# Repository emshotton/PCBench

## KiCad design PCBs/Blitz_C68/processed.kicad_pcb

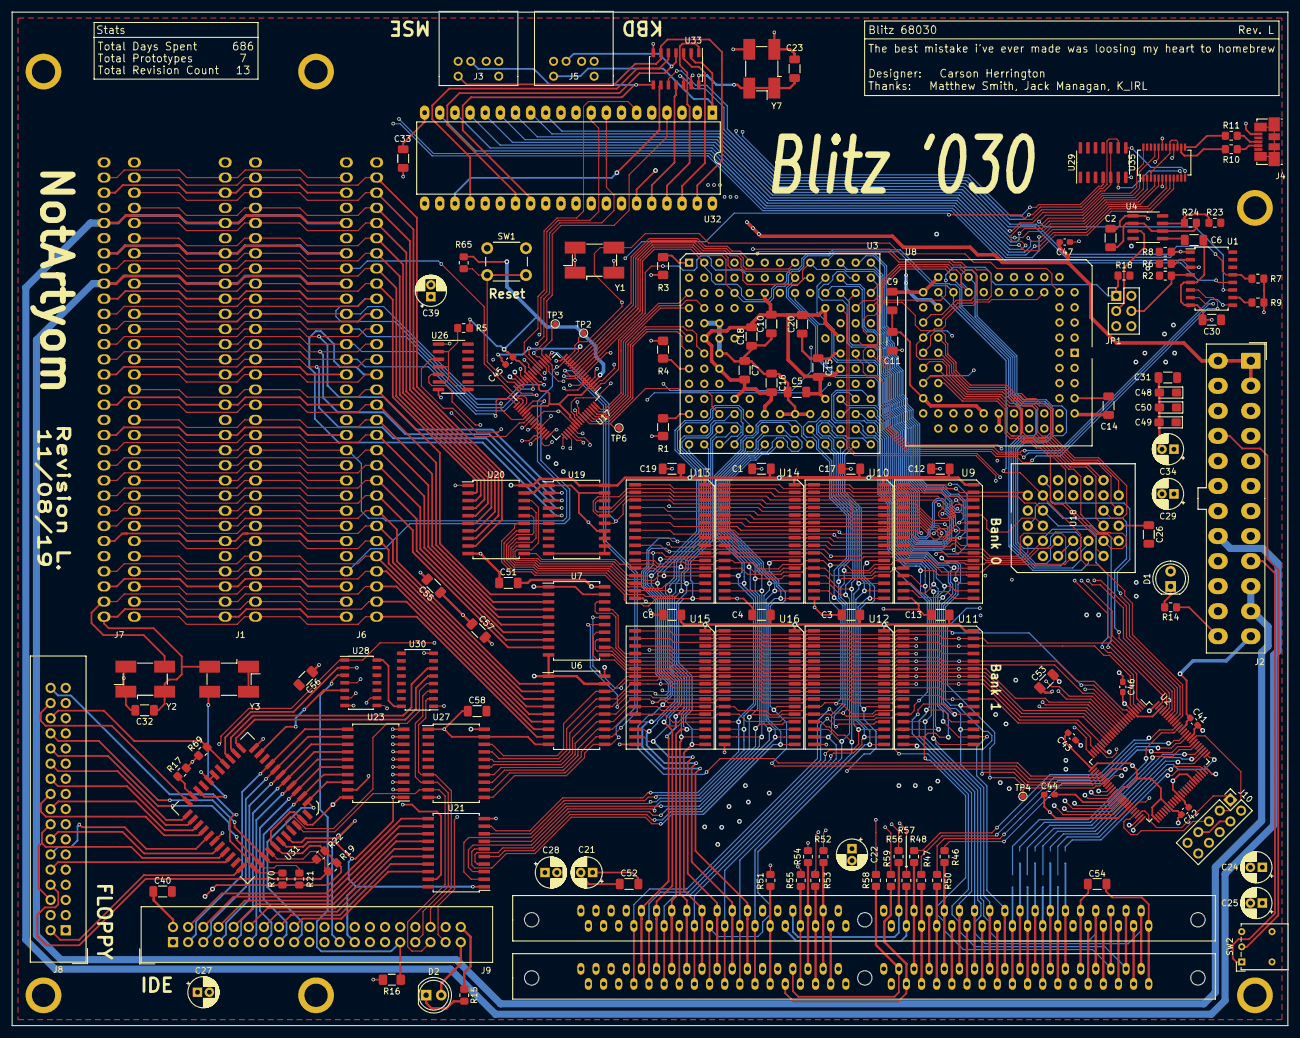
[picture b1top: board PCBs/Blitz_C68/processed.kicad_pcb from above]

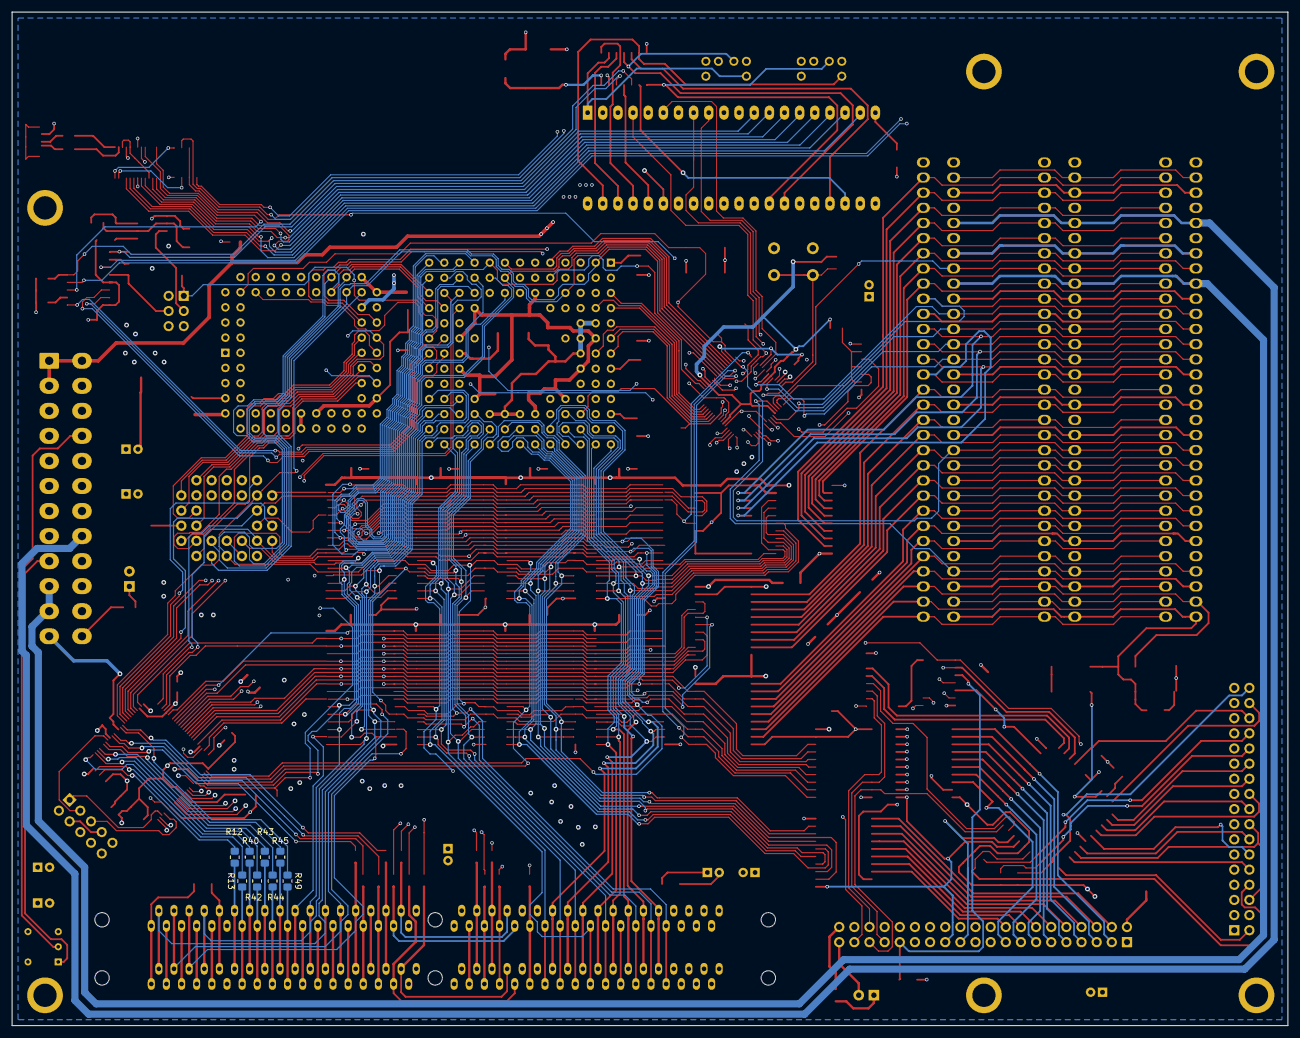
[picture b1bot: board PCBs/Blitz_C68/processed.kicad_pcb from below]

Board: 4 copper layers, 214.0 x 170.0 mm, 160 parts (8 on the bottom side), 278 nets.

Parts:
C1, C3, C4, C5, C7, C8, C9, C10, C11, C12, C13, C14, C15, C16, C17, C18, C19, C20, C23, C26, C30, C31, C32, C33, C40, C51, C52, C53, C54, C55, C56, C57, C58: 100nf; C_1206_3216Metric_Pad1.33x1.80mm_HandSolder
C2: .47uF; C_1206_3216Metric_Pad1.33x1.80mm_HandSolder
C6: 100pF; C_1206_3216Metric_Pad1.33x1.80mm_HandSolder
C21, C22, C24, C25, C27, C28, C29, C34: 47uf; CP_Radial_D5.0mm_P2.00mm
C39: 10uf; CP_Radial_D5.0mm_P2.00mm
C41, C42, C43, C44, C45, C46, C47: 100nf; C_0603_1608Metric_Pad1.08x0.95mm_HandSolder
C48, C49, C50: 1uf; CP_EIA-3216-10_Kemet-I_Pad1.58x1.35mm_HandSolder
D1, D2: LED; LED_D5.0mm
H1, H2, H3, H4, H5, H6: PTH_mount; atx_mounting_hole
J1, J6, J7: ISAx8; ISA_x8_VERT
J2: ATX24; Molex_Mini-Fit_Jr_5566-24A_2x12_P4.20mm_Vertical
J3: MSE; PS2
J4: USB; USB_Micro-B_Molex_47346-0001
J5: KBD; PS2
J8: FLOPPY; IDC-Header_2x17_P2.54mm_Vertical
J9: IDE; IDC-Header_2x20_P2.54mm_Vertical
J10: JTAG; PinHeader_2x05_P2.54mm_Vertical
JP1: Conn_02x03_Odd_Even; PinHeader_2x03_P2.54mm_Vertical
R1, R3, R4, R16: 10k; R_1206_3216Metric_Pad1.42x1.75mm_HandSolder
R2, R5, R6, R7, R8, R9, R14, R18, R23, R24, R65: 10k; R_0805_2012Metric_Pad1.20x1.40mm_HandSolder
R10, R11: 27; R_0805_2012Metric_Pad1.20x1.40mm_HandSolder
R12, R13, R40, R42, R43, R44, R45, R46, R47, R48, R49, R50, R51, R52, R53, R54, R55, R56, R57, R58, R59: 22; R_0805_2012Metric_Pad1.20x1.40mm_HandSolder
R15: 330; R_0805_2012Metric_Pad1.20x1.40mm_HandSolder
R17, R19, R21, R22, R69, R70: 150; R_0805_2012Metric_Pad1.20x1.40mm_HandSolder
SW1: RESET; SW_PUSH_6mm
SW2: PWR; SW_Lever_1P2T_NKK_GW12LxH
TP2, TP3, TP4, TP6: TestPoint; TestPoint_Pad_D1.0mm
U1: 74LS148; SOIC-16W_5.3x10.2mm_P1.27mm
U2: XC9572XL-TQ100; TQFP-100_14x14mm_P0.5mm
U3: M68030; PGA120
U4: TLC555; SOIC-8_3.9x4.9mm_P1.27mm
U5, U24: SIMM_72
U6, U7, U19, U20, U21, U23, U27: 74LS245; SOIC-20W_7.5x12.8mm_P1.27mm
U8: M68882_PLCC; PLCC-68_THT-Socket
U9, U10, U11, U12, U13, U14, U15, U16: AS6C4008; SOIC-32
U17: XC9572XL-VQ64; TQFP-64_10x10mm_P0.5mm
U18: SST39SF040; PLCC-32_TH
U26: 7407; SOIC-14_3.9x8.7mm_P1.27mm
U28: 7404; SOIC-14_3.9x8.7mm_P1.27mm
U29: 7432; SOIC-14_3.9x8.7mm_P1.27mm
U30: 74hc139; SOIC-16_3.9x9.9mm_P1.27mm
U31: WD37C65; PLCC-44
U32: 8042; DIP-40_W15.24mm_LongPads
U33: 74LS06; SOIC-14_3.9x8.7mm_P1.27mm
U35: FT240XS; SSOP-24_3.9x8.7mm_P0.635mm
Y1: 20MHz; Oscillator_SMD_EuroQuartz_XO91-4Pin_7.0x5.0mm_HandSoldering
Y2: 14.316MHz; Oscillator_SMD_EuroQuartz_XO91-4Pin_7.0x5.0mm_HandSoldering
Y3: 16MHz; Oscillator_SMD_EuroQuartz_XO91-4Pin_7.0x5.0mm_HandSoldering
Y7: 8MHz; Oscillator_SMD_EuroQuartz_XO91-4Pin_7.0x5.0mm_HandSoldering

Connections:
100Hz: JP1.3, U4.3 (OUT)
!READ: J9.25, U18.24 (OE), U21.1 (~DIR), U23.1 (~DIR), U28.8, U29.4, U31.1 (/RD), U32.8 (RD)
+3V3: C41.2, C42.2, C43.2, C44.2, C45.2, C46.2, C47.2, J2.1 (3V3), J2.2 (3V3), J2.12 (3V3), J2.13 (3V3), J10.4 (VREF), J10.7 (VCC), R5.1, R65.1, U2.5 (VCC), U2.26 (VCCIO), U2.38 (VCCIO), U2.51 (VCCIO), U2.57 (VCC), U2.88 (VCCIO), U2.98 (VCC), U17.3 (VCC), U17.26 (VCCIO), U17.37 (VCC), U17.55 (VCCIO)
+5V: C1.2, C3.2, C4.2, C5.2, C7.2, C8.2, C9.2, C10.2, C11.2, C12.2, C13.2, C14.2, C15.2, C16.2, C17.2, C18.2, C19.2, C20.2, C21.1, C22.1, C23.2, C24.1, C25.1, C26.2, C27.1, C28.1, C29.1, C30.2, C31.2, C32.2, C33.2, C34.1, C39.1, C40.2, C48.1, C49.1, C50.1, C51.2, C52.2, C53.2, C54.2, C55.2, C56.2, C57.2, C58.2, D1.2 (A), J1.B3 (+5V), J1.B15 (DACK3), J1.B17 (DACK1), J1.B19 (REFRESH), J1.B26 (DACK2), J1.B29 (+5V), J2.4 (5V), J2.6 (5V), J2.21 (5V), J2.22 (5V), J2.23 (5V), J3.4 (VCC), J5.4 (VCC), J6.B3 (+5V), J6.B15 (DACK3), J6.B17 (DACK1), J6.B19 (REFRESH), J6.B26 (DACK2), J6.B29 (+5V), J7.B3 (+5V), J7.B15 (DACK3), J7.B17 (DACK1), J7.B19 (REFRESH), J7.B26 (DACK2), J7.B29 (+5V), J9.29, R1.1, R2.1, R3.1, R4.1, R6.1, R7.1, R8.1, R9.1, R17.2, R18.1, R19.2, R21.2, R22.2, R23.2, R69.2, R70.2, U1.16 (VCC), U3.C6 (VCC), U3.D4 (VCC), U3.D10 (VCC), U3.F2 (VCC), U3.F11 (VCC), U3.H3 (VCC), U3.H11 (VCC), U3.K4 (VCC), U3.K10 (VCC), U3.L6 (VCC), U4.4 (~RESET), U4.8 (VDD), U5.10 (VCC), U5.30 (VCC), U5.59 (VCC), U6.20 (VCC), U7.20 (VCC), U8.10 (VCC), U8.16 (VCC), U8.17 (VCC), U8.18 (SIZE), U8.26 (A0), U8.27 (VCC), U8.43 (VCC), U8.52 (VCC), U8.53 (VCC), U8.61 (VCC), U9.32 (VCC), U10.32 (VCC), U11.32 (VCC), U12.32 (VCC), U13.32 (VCC), U14.32 (VCC), U15.32 (VCC), U16.32 (VCC), U18.32 (VCC), U19.20 (VCC), U20.20 (VCC), U21.20 (VCC), U23.20 (VCC), U24.10 (VCC), U24.30 (VCC), U24.59 (VCC), U26.14 (VCC), U27.20 (VCC), U28.14 (VCC), U29.14 (VCC), U30.16 (VCC), U31.5 (/DACK), U31.44 (VCC), U32.5 (SS), U32.25 (PROG), U32.26 (VDD), U32.40 (VCC), U33.14 (VCC), U35.18 (VCC), Y1.1 (E), Y1.4 (VCC), Y2.1 (E), Y2.4 (VCC), Y3.1 (E), Y3.4 (VCC), Y7.1 (E), Y7.4 (VCC)
+12V: J1.B9 (+12v), J2.10 (12V), J2.11 (12V), J6.B9 (+12v), J7.B9 (+12v)
-5V: J1.B5 (-5V), J2.20 (-5V), J6.B5 (-5V), J7.B5 (-5V)
-12V: J1.B7 (-12V), J2.14 (-12), J6.B7 (-12V), J7.B7 (-12V)
/A0: U3.A2 (A0), U6.11 (B7), U17.8, U18.12 (A0), U27.11 (B7), U32.9 (A0)
/A1: U3.C4 (A1), U6.12 (B6), U8.25 (A1), U17.9, U18.11 (A1), U27.12 (B6)
/A2: U2.93, U3.D13 (A2), U6.13 (B5), U8.24 (A2), U9.12 (A0), U10.12 (A0), U11.12 (A0), U12.12 (A0), U13.12 (A0), U14.12 (A0), U15.12 (A0), U16.12 (A0), U18.10 (A2), U27.13 (B5)
/A3: U2.94, U3.D12 (A3), U6.14 (B4), U8.23 (A3), U9.11 (A1), U10.11 (A1), U11.11 (A1), U12.11 (A1), U13.11 (A1), U14.11 (A1), U15.11 (A1), U16.11 (A1), U18.9 (A3), U27.14 (B4)
/A4: U2.96, U3.C13 (A4), U6.15 (B3), U8.22 (A4), U9.10 (A2), U10.10 (A2), U11.10 (A2), U12.10 (A2), U13.10 (A2), U14.10 (A2), U15.10 (A2), U16.10 (A2), U18.8 (A4), U27.15 (B3)
/A5: U2.97, U3.C12 (A5), U6.16 (B2), U9.9 (A3), U10.9 (A3), U11.9 (A3), U12.9 (A3), U13.9 (A3), U14.9 (A3), U15.9 (A3), U16.9 (A3), U18.7 (A5), U27.16 (B2)
/A6: U2.3 (I/O/GTS1), U3.D11 (A6), U6.17 (B1), U9.8 (A4), U10.8 (A4), U11.8 (A4), U12.8 (A4), U13.8 (A4), U14.8 (A4), U15.8 (A4), U16.8 (A4), U18.6 (A6), U27.17 (B1)
/A7: U2.18, U3.B13 (A7), U6.18 (B0), U9.7 (A5), U10.7 (A5), U11.7 (A5), U12.7 (A5), U13.7 (A5), U14.7 (A5), U15.7 (A5), U16.7 (A5), U18.5 (A7), U27.18 (B0)
/A8: U2.16, U3.B12 (A8), U7.11 (B7), U9.6 (A6), U10.6 (A6), U11.6 (A6), U12.6 (A6), U13.6 (A6), U14.6 (A6), U15.6 (A6), U16.6 (A6), U18.27 (A8)
/A9: U2.10, U3.C11 (A9), U7.12 (B6), U9.5 (A7), U10.5 (A7), U11.5 (A7), U12.5 (A7), U13.5 (A7), U14.5 (A7), U15.5 (A7), U16.5 (A7), U18.26 (A9)
/A10: U2.13, U3.A13 (A10), U7.13 (B5), U9.27 (A8), U10.27 (A8), U11.27 (A8), U12.27 (A8), U13.27 (A8), U14.27 (A8), U15.27 (A8), U16.27 (A8), U18.23 (A10)
/A11: U2.17, U3.C10 (A11), U7.14 (B4), U9.26 (A9), U10.26 (A9), U11.26 (A9), U12.26 (A9), U13.26 (A9), U14.26 (A9), U15.26 (A9), U16.26 (A9), U18.25 (A11)
/A12: U2.23 (I/O/GCK2), U3.B11 (A12), U7.15 (B3), U9.23 (A10), U10.23 (A10), U11.23 (A10), U12.23 (A10), U13.23 (A10), U14.23 (A10), U15.23 (A10), U16.23 (A10), U18.4 (A12)
/A13: U2.20, U3.A12 (A13), U7.16 (B2), U9.25 (A11), U10.25 (A11), U11.25 (A11), U12.25 (A11), U13.25 (A11), U14.25 (A11), U15.25 (A11), U16.25 (A11), U18.28 (A13)
/A14: U2.92, U3.B10 (A14), U7.17 (B1), U9.4 (A12), U10.4 (A12), U11.4 (A12), U12.4 (A12), U13.4 (A12), U14.4 (A12), U15.4 (A12), U16.4 (A12), U18.29 (A14)
/A15: U2.6, U3.A11 (A15), U7.18 (B0), U9.28 (A13), U10.28 (A13), U11.28 (A13), U12.28 (A13), U13.28 (A13), U14.28 (A13), U15.28 (A13), U16.28 (A13), U18.3 (A15)
/A16: U2.95, U3.B9 (A16), U9.3 (A14), U10.3 (A14), U11.3 (A14), U12.3 (A14), U13.3 (A14), U14.3 (A14), U15.3 (A14), U16.3 (A14), U17.17 (I/O/GCK3), U18.2 (A16), U19.15 (B3)
/A17: U2.99 (I/O/GSR), U3.A10 (A17), U9.31 (A15), U10.31 (A15), U11.31 (A15), U12.31 (A15), U13.31 (A15), U14.31 (A15), U15.31 (A15), U16.31 (A15), U18.30 (A17), U19.16 (B2)
/A18: U2.1 (I/O/GTS3), U3.C8 (A18), U9.2 (A16), U10.2 (A16), U11.2 (A16), U12.2 (A16), U13.2 (A16), U14.2 (A16), U15.2 (A16), U16.2 (A16), U18.1 (A18), U19.17 (B1)
/A19: U2.4 (I/O/GTS2), U3.A9 (A19), U9.30 (A17), U10.30 (A17), U11.30 (A17), U12.30 (A17), U13.30 (A17), U14.30 (A17), U15.30 (A17), U16.30 (A17), U17.10, U19.18 (B0)
/A20: U2.8, U3.B8 (A20), U9.1 (A18), U10.1 (A18), U11.1 (A18), U12.1 (A18), U13.1 (A18), U14.1 (A18), U15.1 (A18), U16.1 (A18), U17.11
/A21: U2.9, U3.A8 (A21), U17.12
/A22: U2.11, U3.B7 (A22)
/A23: U2.12, U3.A7 (A23)
/A24: U2.14, U3.A6 (A24)
/A25: U2.15, U3.B6 (A25)
/A26: U3.A5 (A26), U17.13
/A27: U3.B5 (A27), U17.1
/CAS0: R52.1, U5.40 (CAS0), U24.40 (CAS0)
/CAS1: R53.1, U5.41 (CAS1), U24.41 (CAS1)
/CAS2: R54.1, U5.42 (CAS2), U24.42 (CAS2)
/CAS3: R55.1, U5.43 (CAS3), U24.43 (CAS3)
/D0: U3.K13 (D0), U5.2 (DQ0), U8.3 (D0), U9.13 (D0), U11.13 (D0), U24.2 (DQ0)
/D1: U3.K12 (D1), U5.4 (DQ1), U8.2 (D1), U9.14 (D1), U11.14 (D1), U24.4 (DQ1)
/D2: U3.L13 (D2), U5.6 (DQ2), U8.1 (D2), U9.15 (D2), U11.15 (D2), U24.6 (DQ2)
/D3: U3.M13 (D3), U5.8 (DQ3), U8.68 (D3), U9.17 (D3), U11.17 (D3), U24.8 (DQ3)
/D4: U3.L12 (D4), U5.20 (DQ4), U8.67 (D4), U9.18 (D4), U11.18 (D4), U24.20 (DQ4)
/D5: U3.K11 (D5), U5.22 (DQ5), U8.66 (D5), U9.19 (D5), U11.19 (D5), U24.22 (DQ5)
/D6: U3.M12 (D6), U5.24 (DQ6), U8.65 (D6), U9.20 (D6), U11.20 (D6), U24.24 (DQ6)
/D7: U3.L11 (D7), U5.26 (DQ7), U8.64 (D7), U9.21 (D7), U11.21 (D7), U24.26 (DQ7)
/D8: U3.N13 (D8), U5.49 (DQ8), U8.62 (D8), U10.13 (D0), U12.13 (D0), U24.49 (DQ8)
/D9: U3.M11 (D9), U5.51 (DQ9), U8.60 (D9), U10.14 (D1), U12.14 (D1), U24.51 (DQ9)
/D10: U3.L10 (D10), U5.53 (DQ10), U8.59 (D10), U10.15 (D2), U12.15 (D2), U24.53 (DQ10)
/D11: U3.N12 (D11), U5.55 (DQ11), U8.58 (D11), U10.17 (D3), U12.17 (D3), U24.55 (DQ11)
/D12: U3.M10 (D12), U5.57 (DQ12), U8.57 (D12), U10.18 (D4), U12.18 (D4), U24.57 (DQ12)
/D13: U3.N11 (D13), U5.61 (DQ13), U8.56 (D13), U10.19 (D5), U12.19 (D5), U24.61 (DQ13)
/D14: U3.M9 (D14), U5.63 (DQ14), U8.55 (D14), U10.20 (D6), U12.20 (D6), U24.63 (DQ14)
/D15: U3.N10 (D15), U5.65 (DQ15), U8.54 (D15), U10.21 (D7), U12.21 (D7), U24.65 (DQ15)
/D16: U3.N9 (D16), U5.3 (DQ16), U8.50 (D16), U14.13 (D0), U16.13 (D0), U21.9 (A7), U24.3 (DQ16)
/D17: U3.M8 (D17), U5.5 (DQ17), U8.49 (D17), U14.14 (D1), U16.14 (D1), U21.8 (A6), U24.5 (DQ17)
/D18: U3.N8 (D18), U5.7 (DQ18), U8.48 (D18), U14.15 (D2), U16.15 (D2), U21.7 (A5), U24.7 (DQ18)
/D19: U3.N7 (D19), U5.9 (DQ19), U8.47 (D19), U14.17 (D3), U16.17 (D3), U21.6 (A4), U24.9 (DQ19)
/D20: U3.M7 (D20), U5.21 (DQ20), U8.46 (D20), U14.18 (D4), U16.18 (D4), U21.5 (A3), U24.21 (DQ20)
/D21: U3.N6 (D21), U5.23 (DQ21), U8.45 (D21), U14.19 (D5), U16.19 (D5), U21.4 (A2), U24.23 (DQ21)
/D22: U3.M6 (D22), U5.25 (DQ22), U8.44 (D22), U14.20 (D6), U16.20 (D6), U21.3 (A1), U24.25 (DQ22)
/D23: U3.N5 (D23), U5.27 (DQ23), U8.42 (D23), U14.21 (D7), U16.21 (D7), U21.2 (A0), U24.27 (DQ23)
/D24: U3.M5 (D24), U5.50 (DQ24), U8.40 (D24), U13.13 (D0), U15.13 (D0), U18.13 (D0), U20.18 (B0), U23.2 (A0), U24.50 (DQ24), U32.12 (D0), U35.24 (DATA0)
/D25: U3.N4 (D25), U5.52 (DQ25), U8.39 (D25), U13.14 (D1), U15.14 (D1), U18.14 (D1), U20.17 (B1), U23.3 (A1), U24.52 (DQ25), U32.13 (D1), U35.4 (DATA1)
/D26: U3.N3 (D26), U5.54 (DQ26), U8.38 (D26), U13.15 (D2), U15.15 (D2), U18.15 (D2), U20.16 (B2), U23.4 (A2), U24.54 (DQ26), U32.14 (D2), U35.2 (DATA2)
/D27: U3.M4 (D27), U5.56 (DQ27), U8.37 (D27), U13.17 (D3), U15.17 (D3), U18.17 (D3), U20.15 (B3), U23.5 (A3), U24.56 (DQ27), U32.15 (D3), U35.9 (DATA3)
/D28: U3.N2 (D28), U5.58 (DQ28), U8.36 (D28), U13.18 (D4), U15.18 (D4), U18.18 (D4), U20.14 (B4), U23.6 (A4), U24.58 (DQ28), U32.16 (D4), U35.1 (DATA4)
/D29: U3.M3 (D29), U5.60 (DQ29), U8.35 (D29), U13.19 (D5), U15.19 (D5), U18.19 (D5), U20.13 (B5), U23.7 (A5), U24.60 (DQ29), U32.17 (D5), U35.7 (DATA5)
/D30: U3.L4 (D30), U5.62 (DQ30), U8.34 (D30), U13.20 (D6), U15.20 (D6), U18.20 (D6), U20.12 (B6), U23.8 (A6), U24.62 (DQ30), U32.18 (D6), U35.8 (DATA6)
/D31: U3.N1 (D31), U5.64 (DQ31), U8.33 (D31), U13.21 (D7), U15.21 (D7), U18.21 (D7), U20.11 (B7), U23.9 (A7), U24.64 (DQ31), U32.19 (D7), U35.5 (DATA7)
/IA0: J1.A31 (A0), J6.A31 (A0), J7.A31 (A0), U6.9 (A7)
/IA1: J1.A30 (A1), J6.A30 (A1), J7.A30 (A1), U6.8 (A6)
/IA2: J1.A29 (A2), J6.A29 (A2), J7.A29 (A2), U6.7 (A5)
/IA3: J1.A28 (A3), J6.A28 (A3), J7.A28 (A3), U6.6 (A4)
/IA4: J1.A27 (A4), J6.A27 (A4), J7.A27 (A4), U6.5 (A3)
/IA5: J1.A26 (A5), J6.A26 (A5), J7.A26 (A5), U6.4 (A2)
/IA6: J1.A25 (A6), J6.A25 (A6), J7.A25 (A6), U6.3 (A1)
/IA7: J1.A24 (A7), J6.A24 (A7), J7.A24 (A7), U6.2 (A0)
/IA8: J1.A23 (A8), J6.A23 (A8), J7.A23 (A8), U7.9 (A7)
/IA9: J1.A22 (A9), J6.A22 (A9), J7.A22 (A9), U7.8 (A6)
/IA10: J1.A21 (A10), J6.A21 (A10), J7.A21 (A10), U7.7 (A5)
/IA11: J1.A20 (A11), J6.A20 (A11), J7.A20 (A11), U7.6 (A4)
/IA12: J1.A19 (A12), J6.A19 (A12), J7.A19 (A12), U7.5 (A3)
/IA13: J1.A18 (A13), J6.A18 (A13), J7.A18 (A13), U7.4 (A2)
/IA14: J1.A17 (A14), J6.A17 (A14), J7.A17 (A14), U7.3 (A1)
/IA15: J1.A16 (A15), J6.A16 (A15), J7.A16 (A15), U7.2 (A0)
/IA16: J1.A15 (A16), J6.A15 (A16), J7.A15 (A16), U19.5 (A3)
/IA17: J1.A14 (A17), J6.A14 (A17), J7.A14 (A17), U19.4 (A2)
/IA18: J1.A13 (A18), J6.A13 (A18), J7.A13 (A18), U19.3 (A1)
/IA19: J1.A12 (A19), J6.A12 (A19), J7.A12 (A19), U19.2 (A0)
/ID0: J1.A9 (D0), J6.A9 (D0), J7.A9 (D0), U20.2 (A0)
/ID1: J1.A8 (D1), J6.A8 (D1), J7.A8 (D1), U20.3 (A1)
/ID2: J1.A7 (D2), J6.A7 (D2), J7.A7 (D2), U20.4 (A2)
/ID3: J1.A6 (D3), J6.A6 (D3), J7.A6 (D3), U20.5 (A3)
/ID4: J1.A5 (D4), J6.A5 (D4), J7.A5 (D4), U20.6 (A4)
/ID5: J1.A4 (D5), J6.A4 (D5), J7.A4 (D5), U20.7 (A5)
/ID6: J1.A3 (D6), J6.A3 (D6), J7.A3 (D6), U20.8 (A6)
/ID7: J1.A2 (D7), J6.A2 (D7), J7.A2 (D7), U20.9 (A7)
/IOA0: J9.35, U27.9 (A7), U31.4 (A0)
/IOA1: J9.33, U27.8 (A6), U30.3 (A)
/IOA2: J9.36, U27.7 (A5), U30.2 (B)
/IOD16: J9.4, U21.11 (B7)
/IOD17: J9.6, U21.12 (B6)
/IOD18: J9.8, U21.13 (B5)
/IOD19: J9.10, U21.14 (B4)
/IOD20: J9.12, U21.15 (B3)
/IOD21: J9.14, U21.16 (B2)
/IOD22: J9.16, U21.17 (B1)
/IOD23: J9.18, U21.18 (B0)
/IOD24: J9.17, U23.18 (B0), U31.7 (DB0)
/IOD25: J9.15, U23.17 (B1), U31.8 (DB1)
/IOD26: J9.13, U23.16 (B2), U31.9 (DB2)
/IOD27: J9.11, U23.15 (B3), U31.10 (DB3)
/IOD28: J9.9, U23.14 (B4), U31.11 (DB4)
/IOD29: J9.7, U23.13 (B5), U31.12 (DB5)
/IOD30: J9.5, U23.12 (B6), U31.13 (DB6)
/IOD31: J9.3, U23.11 (B7), U31.14 (DB7)
/QA0: R12.1, U5.12 (A0), U24.12 (A0)
/QA1: R13.1, U5.13 (A1), U24.13 (A1)
/QA2: R40.1, U5.14 (A2), U24.14 (A2)
/QA3: R42.1, U5.15 (A3), U24.15 (A3)
/QA4: R43.1, U5.16 (A4), U24.16 (A4)
/QA5: R44.1, U5.17 (A5), U24.17 (A5)
/QA6: R45.1, U5.18 (A6), U24.18 (A6)
/QA7: R46.1, U5.28 (A7), U24.28 (A7)
/QA8: R47.1, U5.31 (A8), U24.31 (A8)
/QA9: R48.1, U5.32 (A9), U24.32 (A9)
/QA10: R49.1, U5.19 (A10), U24.19 (A10)
/QA11: R50.1, U5.29 (A11), U24.29 (A11)
/RAS0: R56.1, U5.34 (RAS2), U5.44 (RAS0)
/RAS1: R57.1, U5.33 (RAS3), U5.45 (RAS1)
/RAS2: R58.1, U24.34 (RAS2), U24.44 (RAS0)
/RAS3: R59.1, U24.33 (RAS3), U24.45 (RAS1)
AS: U3.J2 (AS), U8.21 (AS), U17.2 (I/O/GTS2)
BYTE0: U2.30, U9.22 (~CS), U11.22 (~CS), U17.52
BYTE1: U2.29, U10.22 (~CS), U12.22 (~CS), U17.51
BYTE2: U2.28, U14.22 (~CS), U16.22 (~CS), U17.50
BYTE3: U2.27 (I/O/GCK3), U13.22 (~CS), U15.22 (~CS), U17.49
CDIS: U3.H12 (CDIS), U17.23
CLK: J1.B20 (CLK), J6.B20 (CLK), J7.B20 (CLK), TP2.1, U2.22 (I/O/GCK1), U3.E1 (CLK), U8.11 (CLK), U17.15 (I/O/GCK1), Y1.3 (OUT)
DRAM_CS: TP4.1, U2.32, U17.42
DRW: R51.1, U5.47 (R/W), U24.47 (R/W)
DS: U3.K2 (DS), U8.20 (DS), U17.4
DSACK0: U3.F1 (DSACK0), U8.31 (DSACK0), U17.60
DSACK1: U3.G2 (DSACK1), U8.32 (DSACK1), U17.61
DTACK_BUS: R5.2, U17.34, U26.2, U26.4, U26.6
ECS: TP3.1, U3.M2 (ECS), U17.18
FC0: U3.D2 (FC0), U17.63
FC1: U3.C1 (FC1), U17.64 (I/O/GSR)
FC2: U3.D1 (FC2), U17.62
FLOPPY: U17.20, U30.1 (~EN)
FPU: U8.29 (CS), U17.57
FTDI_CS: U17.56, U29.5, U29.10
GND: C1.1, C2.1, C3.1, C4.1, C5.1, C6.1, C7.1, C8.1, C9.1, C10.1, C11.1, C12.1, C13.1, C14.1, C15.1, C16.1, C17.1, C18.1, C19.1, C20.1, C21.2, C22.2, C23.1, C24.2, C25.2, C26.1, C27.2, C28.2, C29.2, C30.1, C31.1, C32.1, C33.1, C34.2, C39.2, C40.1, C41.1, C42.1, C43.1, C44.1, C45.1, C46.1, C47.1, C48.2, C49.2, C50.2, C51.1, C52.1, C53.1, C54.1, C55.1, C56.1, C57.1, C58.1, H1.1, H2.1, H3.1, H4.1, H5.1, H6.1, J1.A11 (AEN), J1.B1 (GND), J1.B10 (GND), J1.B31 (GND), J2.3 (GND), J2.5 (GND), J2.7 (GND), J2.15 (GND), J2.17 (GND), J2.18 (GND), J2.19 (GND), J2.24 (GND), J3.3 (GND), J4.5 (GND), J5.3 (GND), J6.A11 (AEN), J6.B1 (GND), J6.B10 (GND), J6.B31 (GND), J7.A11 (AEN), J7.B1 (GND), J7.B10 (GND), J7.B31 (GND), J8.1, J8.3, J8.5, J8.7, J8.9, J8.11, J8.13, J8.15, J8.17, J8.19, J8.21, J8.23, J8.25, J8.27, J8.29, J8.31, J8.33, J9.2, J9.19, J9.22, J9.24, J9.26, J9.30, J9.40, J10.2 (GND), J10.10 (GND), JP1.2, JP1.5, JP1.6, R14.1, R15.1, R16.1, SW1.1 (A), SW2.3 (C), U1.5 (EI), U1.8 (GND), U2.21 (GND), U2.31 (GND), U2.44 (GND), U2.62 (GND), U2.69 (GND), U2.75 (GND), U2.84 (GND), U2.100 (GND), U3.C5 (GND), U3.C7 (GND), U3.C9 (GND), U3.E2 (AVEC), U3.E3 (GND), U3.E11 (GND), U3.F3 (GND), U3.G3 (GND), U3.G11 (GND), U3.J3 (GND), U3.J11 (GND), U3.L5 (GND), U3.L7 (GND), U3.L8 (GND), U3.L9 (GND), U4.1 (GND), U5.1 (GND), U5.39 (GND), U5.72 (GND), U6.1 (~DIR), U6.10 (GND), U6.19 (~CE), U7.1 (~DIR), U7.10 (GND), U7.19 (~CE), U8.5 (GND), U8.6 (GND), U8.7 (GND), U8.8 (GND), U8.9 (GND), U8.12 (GND), U8.14 (GND), U8.19 (GND), U8.30 (GND), U8.41 (GND), U8.51 (GND), U8.63 (GND), U9.16 (GND), U10.16 (GND), U11.16 (GND), U12.16 (GND), U13.16 (GND), U14.16 (GND), U15.16 (GND), U16.16 (GND), U17.14 (GND), U17.21 (GND), U17.41 (GND), U17.54 (GND), U18.16 (GND), U19.1 (~DIR), U19.10 (GND), U19.11 (B7), U19.12 (B6), U19.13 (B5), U19.14 (B4), U19.19 (~CE), U20.10 (GND), U20.19 (~CE)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
HALT: U3.H2 (HALT), U17.16 (I/O/GCK2)
IDE0: J9.37, U17.7
IDE1: J9.38, U17.40
IO_CS: U17.39, U21.19 (~CE), U23.19 (~CE)
IPL0: U1.9 (S0), U3.H13 (IPL0)
IPL1: U1.7 (S1), U3.G13 (IPL1)
IPL2: U1.6 (S2), U3.G12 (IPL2)
IRQ_FLOPPY: U1.3 (I6), U28.6
IRQ_FTDI: U1.11 (I1), U35.21 (~RXF)
IRQ_IDE: U1.12 (I2), U28.4
IRQ_KBD: R8.2, U1.1 (I4), U33.12
IRQ_MSE: R7.2, U1.13 (I3), U33.10
IRQ_SYS: JP1.4, R2.2, U1.4 (I7)
ISA_IRQ0: J1.B25 (IRQ3), J6.B25 (IRQ3), J7.B25 (IRQ3)
ISA_IRQ1: J1.B24 (IRQ4), J6.B24 (IRQ4), J7.B24 (IRQ4)
ISA_IRQ2: J1.B23 (IRQ5), J6.B23 (IRQ5), J7.B23 (IRQ5)
ISA_IRQ3: J1.B22 (IRQ6), J6.B22 (IRQ6), J7.B22 (IRQ6)
ISA_IRQ4: J1.B21 (IRQ7), J6.B21 (IRQ7), J7.B21 (IRQ7)
I_DIR: U17.24, U20.1 (~DIR)
KBD_CS: U17.22, U32.6 (CS)
MMUDIS: JP1.1, R18.2, U3.F13 (MMUDIS)
unnamed: C2.2, R24.1, U4.2 (~TRIG), U4.6 (THRES)
unnamed: C6.2, U4.5 (CONT)
unnamed: D1.1 (K), R14.2
unnamed: D2.1 (K), R15.2
unnamed: D2.2 (A), J9.39
unnamed: J1.A10 (IOCHRRDY), J6.A10 (IOCHRRDY), J7.A10 (IOCHRRDY), U17.38
unnamed: J1.B8 (NOWS), J6.B8 (NOWS), J7.B8 (NOWS), U17.35
unnamed: J1.B11 (MEMW), J6.B11 (MEMW), J7.B11 (MEMW), U17.25
unnamed: J1.B12 (MEMR), J6.B12 (MEMR), J7.B12 (MEMR), U17.27
unnamed: J1.B13 (IOW), J6.B13 (IOW), J7.B13 (IOW), U17.32
unnamed: J1.B14 (IOR), J6.B14 (IOR), J7.B14 (IOR), U17.33
unnamed: J1.B28 (ALE), J6.B28 (ALE), J7.B28 (ALE), U17.36
unnamed: J1.B30 (OSC), J6.B30 (OSC), J7.B30 (OSC), Y2.3 (OUT)
unnamed: J2.9 (5VSB), SW2.1 (A)
unnamed: J2.16 (PS_ON), SW2.2 (B)
unnamed: J3.1 (DATA), U32.28 (P11), U33.8
unnamed: J3.5 (CLK), U32.39 (T1), U33.6
unnamed: J4.2 (D-), R10.2
unnamed: J4.3 (D+), R11.2
unnamed: J5.1 (DATA), U32.27 (P10), U33.4
unnamed: J5.5 (CLK), U32.1 (T0), U33.2
unnamed: J8.2, U31.39 (/RWC/RPM)
unnamed: J8.8, R19.1, U31.43 (/IDX)
unnamed: J8.10, U31.37 (/MO2/DS4)
unnamed: J8.12, U31.33 (/DS1)
unnamed: J8.14, U31.35 (/DS2)
unnamed: J8.6, J8.16, U31.36 (/MO1/DS3)
unnamed: J8.18, U31.31 (/DIRC)
unnamed: J8.20, U31.32 (/STEP)
unnamed: J8.22, U31.30 (/WD)
unnamed: J8.24, U31.29 (/WE)
unnamed: J8.26, R21.1, U31.41 (/WP)
unnamed: J8.28, R22.1, U31.42 (/TR00)
unnamed: J8.30, R69.1, U31.21 (/RDD)
unnamed: J8.32, U31.28 (/HS)
unnamed: J8.34, R70.1, U31.40 (/DCHG)
unnamed: J9.27, U26.5
unnamed: J9.31, R16.2, U28.3
unnamed: J10.9 (TDI), U17.28 (TDI)
unnamed: R1.2, U3.L1 (CIIN)
unnamed: R3.2, U3.A1 (BR)
unnamed: R4.2, U3.H1 (BERR)
unnamed: R6.2, U1.2 (I5)
unnamed: R9.2, U1.10 (IO)
unnamed: R10.1, U35.14 (USBDM)
unnamed: R11.1, U35.13 (USBDP)
unnamed: R12.2, U2.72
unnamed: R13.2, U2.74
unnamed: R17.1, U31.27 (PCVAL)
unnamed: R23.1, R24.2, U4.7 (DISCH)
unnamed: R40.2, U2.76
unnamed: R42.2, U2.77
unnamed: R43.2, U2.78
unnamed: R44.2, U2.79
unnamed: R45.2, U2.81
unnamed: R46.2, U2.82
unnamed: R47.2, U2.86
unnamed: R48.2, U2.90
unnamed: R49.2, U2.89
unnamed: R50.2, U2.85
unnamed: R51.2, U2.35
unnamed: R52.2, U2.40
unnamed: R53.2, U2.39
unnamed: R54.2, U2.37
unnamed: R55.2, U2.36
unnamed: R56.2, U2.49
unnamed: R57.2, U2.50
unnamed: R58.2, U2.41
unnamed: R59.2, U2.42
unnamed: R65.2, SW1.2 (B), U17.31
unnamed: U2.25, U26.3
unnamed: U26.1, U35.20 (~TXE)
unnamed: U28.5, U31.16 (IRQ)
unnamed: U29.6, U35.11 (~RD)
unnamed: U29.8, U35.12 (~WR)
unnamed: U30.4 (~Q0), U31.3 (/CS)
unnamed: U30.5 (~Q1), U31.18 (/LDOR)
unnamed: U30.6 (~Q2), U31.19 (/LDCR)
unnamed: U31.26 (XT1), Y3.3 (OUT)
unnamed: U32.3 (X2), Y7.3 (OUT)
unnamed: U32.23 (P22), U33.9
unnamed: U32.24 (P23), U33.5
unnamed: U32.35 (P24/OB), U33.13
unnamed: U32.36 (P25/BF), U33.11
unnamed: U32.37 (P26/DRQ), U33.1
unnamed: U32.38 (P27/DAK), U33.3
unnamed: U35.3 (VCCIO), U35.15 (3V3OUT), U35.17 (VCCIO)
RESET: J9.1, U2.33, U3.F12 (RESET), U8.13 (RESET), U17.19, U28.1, U32.4 (RESET), U35.16 (~RESET)
RESET_N: J1.B2 (RESET), J6.B2 (RESET), J7.B2 (RESET), U28.2, U31.20 (RST)
ROM: U17.44, U18.22 (CE)
RW0: U9.29 (~WE), U10.29 (~WE), U13.29 (~WE), U14.29 (~WE), U17.48
RW1: U11.29 (~WE), U12.29 (~WE), U15.29 (~WE), U16.29 (~WE), U17.46
RW_N: J9.23, TP6.1, U2.91, U3.L3 (R/W), U8.28 (R/W), U17.58, U18.31 (PGM), U28.9, U29.9, U31.2 (/WR), U32.10 (WR)
SIZ0: U3.L2 (SIZ0), U17.5 (I/O/GTS1)
SIZ1: U3.K3 (SIZ1), U17.6
STERM: U3.G1 (STERM), U17.59
TCK: J10.1 (TCK), U2.48 (TCK), U17.30 (TCK)
TDO1: U2.45 (TDI), U17.53 (TDO)
TDO2: J10.3 (TDO), U2.83 (TDO)
TMS: J10.5 (TMS), U2.47 (TMS), U17.29 (TMS)
_RW0: U9.24 (~OE), U10.24 (~OE), U13.24 (~OE), U14.24 (~OE), U17.47
_RW1: U11.24 (~OE), U12.24 (~OE), U15.24 (~OE), U16.24 (~OE), U17.45

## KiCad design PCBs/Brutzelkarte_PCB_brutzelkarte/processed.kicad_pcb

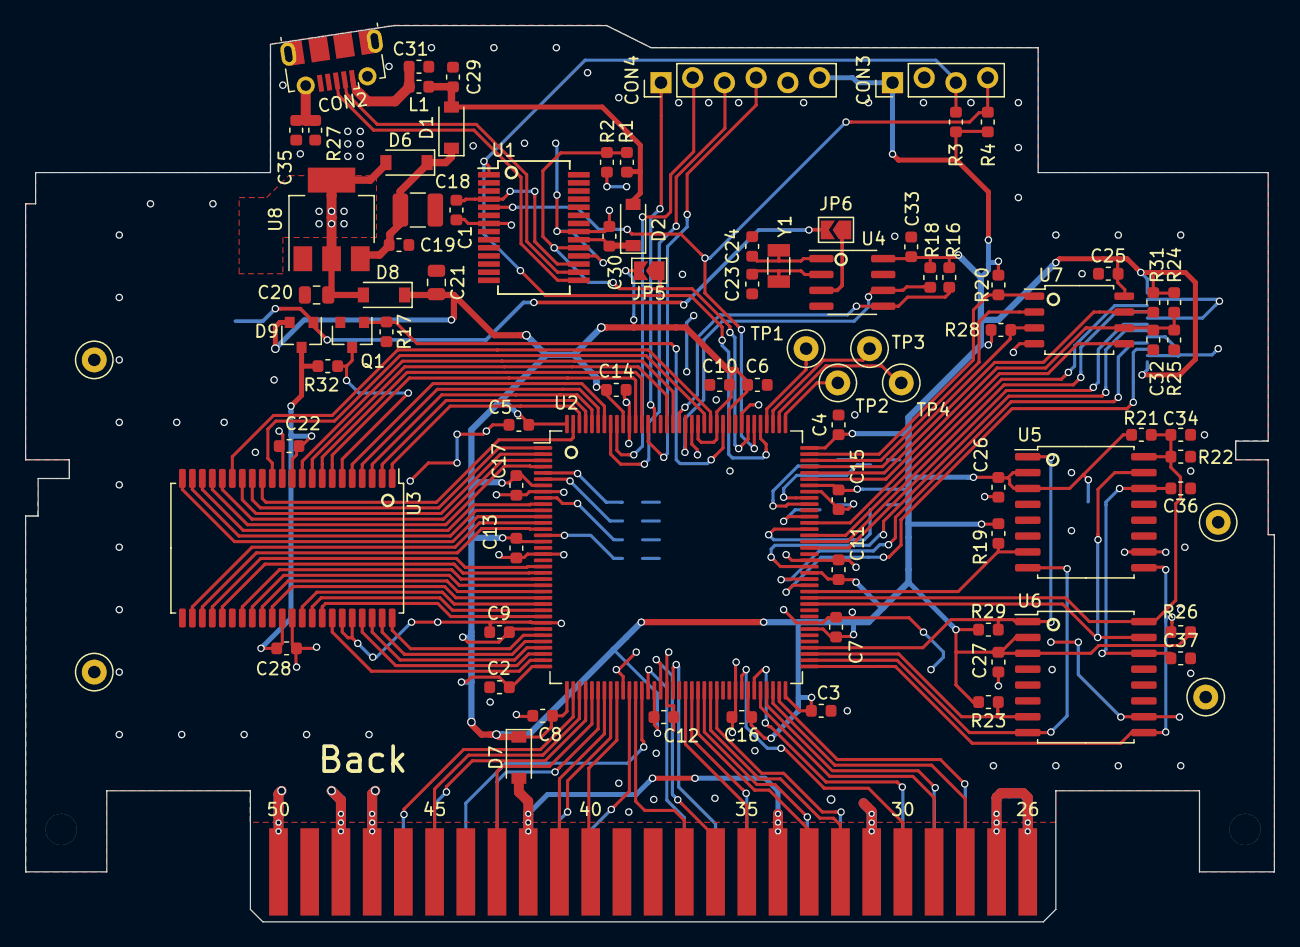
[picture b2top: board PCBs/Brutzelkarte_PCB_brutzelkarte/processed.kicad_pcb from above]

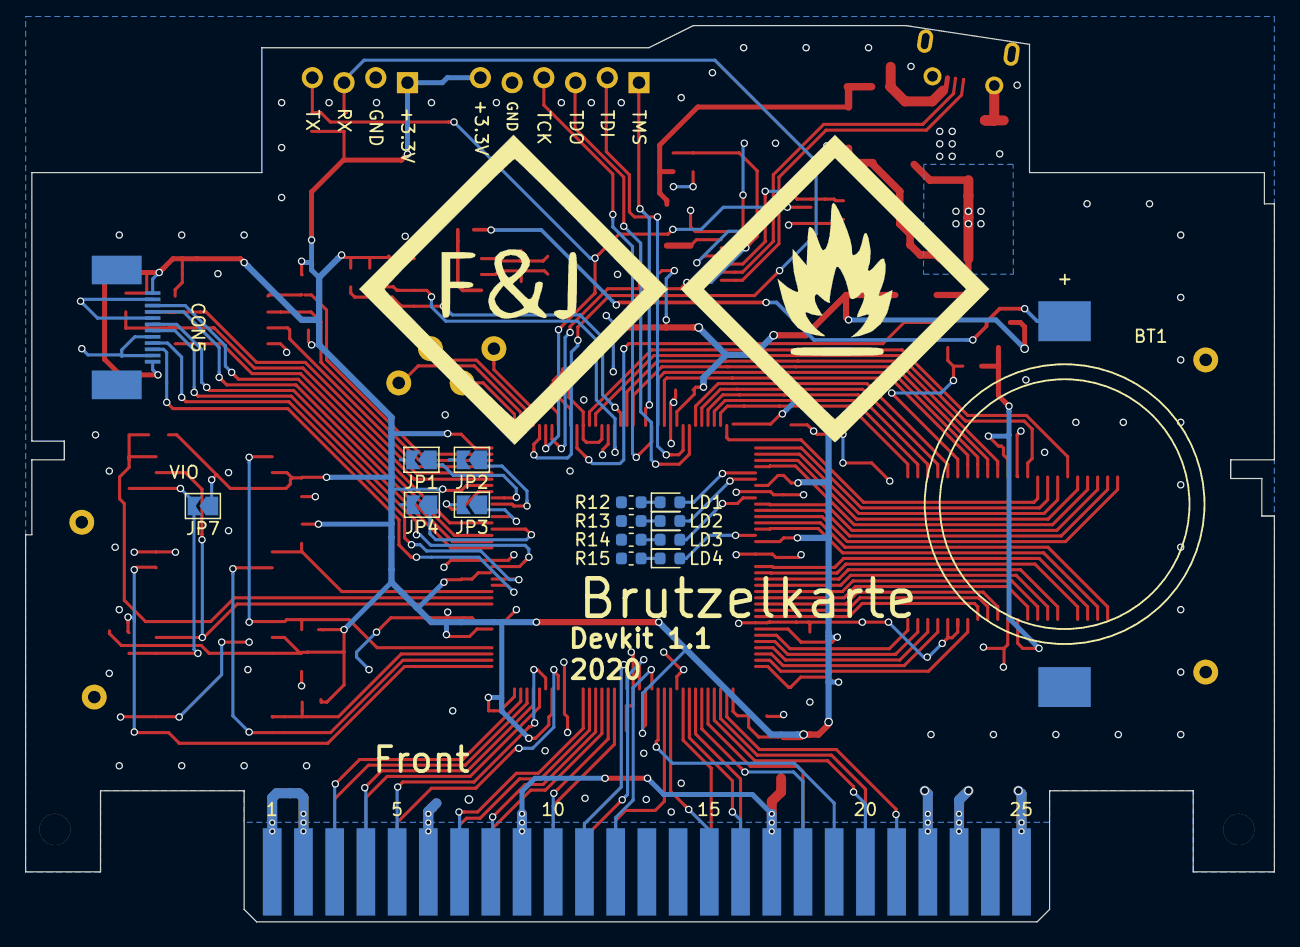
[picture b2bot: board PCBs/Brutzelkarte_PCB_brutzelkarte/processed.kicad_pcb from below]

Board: 2 copper layers, 100.0 x 71.8 mm, 103 parts (16 on the bottom side), 125 nets.

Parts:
BT1: Battery_Cell; BU2032SM
C1, C2, C3, C4, C5, C6, C7, C8, C9, C10, C11, C12, C13, C14, C15, C16, C17, C19, C22, C25, C26, C27, C28, C30, C33, C36, C37: 100n; C_0603_1608Metric
C18: 10u; C_1210_3225Metric
C20: 1u; C_0805_2012Metric
C21: 47u; C_0805_2012Metric
C23, C24: 6-9 pF; C_0603_1608Metric
C29: 4u7; C_0603_1608Metric
C31, C35: 10n; C_0603_1608Metric
C32, C34: ?n; C_0603_1608Metric
CON1: N64-Cartridge; N64-Connector
CON2: USB_B_Micro; USB_Micro-B_Molex-105017-0001
CON3: Conn_01x04; PinHeader_1x04_P2.54mm_NoSolder
CON4: Conn_01x06; PinHeader_1x06_P2.54mm_NoSolder
CON5: Conn_01x12; 12pinFPC_ConnectorP0.5mm
D1, D2, D6, D7, D8: D_Schottky_Small; D_SOD-123
D9: BAT54C; SOT-23
GND1, GND2, GND3, GND4: TestPoint; TestPoint_Loop_D2.50mm_Drill1.0mm
JP1, JP2, JP3, JP4, JP5, JP6, JP7: SolderJumper_2_Open; SolderJumper-2_P1.3mm_Open_TrianglePad1.0x1.5mm
L1: Ferrite; L_0603_1608Metric
LD1, LD2, LD3, LD4: LED_Small; LED_0603_1608Metric
Q1: BSS138K; SOT-23
R1: 6k8; R_0603_1608Metric
R2, R3, R4, R19, R20, R21, R22, R23, R24, R25, R26, R28, R29, R31, R32: 10k; R_0603_1608Metric
R12, R13, R14, R15: 330; R_0603_1608Metric
R16, R18: 4k7; R_0603_1608Metric
R17: 2k2; R_0603_1608Metric
R27: 100k; R_0603_1608Metric
TP1, TP2, TP3, TP4: TestPoint; TestPoint_Loop_D2.50mm_Drill1.0mm
U1: FT232RL; SSOP-28_5.3x10.2mm_P0.65mm
U2: LCMXO2-7000Hx-xTG144x; TQFP-144_20x20mm_P0.5mm
U3: IS62WV12816EBLL; TSOP-II-44_10.16x18.41mm_P0.8mm
U4: MCP7940N; SOIC-8_3.9x4.9mm_P1.27mm
U5, U6: S25FL256S; SOIC-16W_7.5x10.3mm_P1.27mm
U7: W25Q_SOIC8; SOIC-8_5.275x5.275mm_P1.27mm
U8: TLV1117LV; SOT-223
Y1: 32768; Crystal_SMD_3215-2Pin_3.2x1.5mm

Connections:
+3V3: C2.1, C3.1, C4.1, C5.1, C6.1, C7.1, C8.1, C9.1, C10.1, C11.1, C12.1, C13.1, C14.1, C15.1, C16.1, C17.1, C21.1, C25.2, C26.1, C27.1, C33.1, CON3.1, CON4.6, CON5.1, CON5.12, D7.1, D8.1, D9.2, JP5.2, JP7.1, R3.1, R4.1, R16.1, R18.1, R19.1, R20.1, R21.1, R23.1, R24.1, R26.1, R28.1, R29.1, R31.1, U2.7, U2.16, U2.30, U2.36, U2.37, U2.51, U2.66, U2.72, U2.79, U2.88, U2.102, U2.108, U2.118, U2.120, U2.123, U2.135, U2.144, U4.8, U5.2, U5.3, U6.2, U6.3, U7.8
/fpga/BOOT_CS: R20.2, U2.107, U7.1
/fpga/BOOT_IO0: U2.96, U7.5
/fpga/BOOT_IO1: U2.106, U7.2
/fpga/BOOT_IO2: R28.2, U2.105, U7.3
/fpga/BOOT_IO3: R31.2, U2.104, U7.7
/fpga/BOOT_SCK: C32.1, R24.2, R25.1, U2.103, U7.6
/fpga/EXT0: CON5.3, U2.94
/fpga/EXT1: CON5.4, U2.93
/fpga/EXT2: CON5.6, U2.92
/fpga/EXT3: CON5.7, U2.89
/fpga/EXT4: CON5.9, U2.87
/fpga/EXT5: CON5.10, U2.86
/fpga/JP1: JP1.1, U2.100
/fpga/JP2: JP2.1, U2.99
/fpga/JP3: JP3.1, U2.97
/fpga/JP4: JP4.1, U2.95
/fpga/LED1: LD1.2, U2.5
/fpga/LED2: LD2.2, U2.6
/fpga/LED3: LD3.2, U2.9
/fpga/LED4: LD4.2, U2.15
/fpga/N64_AD0: CON1.28, U2.70
/fpga/N64_AD1: CON1.29, U2.68
/fpga/N64_AD2: CON1.30, U2.65
/fpga/N64_AD3: CON1.32, U2.60
/fpga/N64_AD4: CON1.36, U2.52
/fpga/N64_AD5: CON1.37, U2.48
/fpga/N64_AD6: CON1.40, U2.45
/fpga/N64_AD7: CON1.41, U2.43
/fpga/N64_AD8: CON1.16, U2.44
/fpga/N64_AD9: CON1.15, U2.47
/fpga/N64_AD10: CON1.12, U2.50
/fpga/N64_AD11: CON1.11, U2.54
/fpga/N64_AD12: CON1.7, U2.61
/fpga/N64_AD13: CON1.5, U2.67
/fpga/N64_AD14: CON1.4, U2.69
/fpga/N64_AD15: CON1.3, U2.71
/fpga/N64_ALEH: CON1.35, U2.56
/fpga/N64_ALEL: CON1.33, U2.58
/fpga/N64_CIC_DCLK: CON1.43, U2.41
/fpga/N64_CIC_DIO: CON1.18, U2.42
/fpga/N64_CR: CON1.20, U2.40
/fpga/N64_EEP_SDAT: CON1.21, U2.38
/fpga/N64_NMI: CON1.45, U2.39
/fpga/N64_READ: CON1.10, U2.57
/fpga/N64_SI_CLK: CON1.19, U2.49
/fpga/N64_VCC: CON1.9, CON1.17, CON1.34, CON1.42, D7.2
/fpga/N64_WRITE: CON1.8, U2.59
/fpga/RAM_A0: U2.138, U3.5
/fpga/RAM_A1: U2.139, U3.4
/fpga/RAM_A2: U2.140, U3.3
/fpga/RAM_A3: U2.141, U3.2
/fpga/RAM_A4: U2.142, U3.1
/fpga/RAM_A5: U2.31, U3.44
/fpga/RAM_A6: U2.32, U3.43
/fpga/RAM_A7: U2.33, U3.42
/fpga/RAM_A8: U2.21, U3.27
/fpga/RAM_A9: U2.20, U3.26
/fpga/RAM_A10: U2.14, U3.25
/fpga/RAM_A11: U2.13, U3.24
/fpga/RAM_A12: U2.12, U3.22
/fpga/RAM_A13: U2.11, U3.21
/fpga/RAM_A14: U2.10, U3.20
/fpga/RAM_A15: U2.4, U3.19
/fpga/RAM_A16: U2.3, U3.18
/fpga/RAM_CE: Q1.1, R17.1, U2.119
/fpga/RAM_DQ0: U2.133, U3.7
/fpga/RAM_DQ1: U2.132, U3.8
/fpga/RAM_DQ2: U2.128, U3.9
/fpga/RAM_DQ3: U2.127, U3.10
/fpga/RAM_DQ4: U2.122, U3.13
/fpga/RAM_DQ5: U2.143, U3.14
/fpga/RAM_DQ6: U2.1, U3.15
/fpga/RAM_DQ7: U2.2, U3.16
/fpga/RAM_DQ8: U2.22, U3.29
/fpga/RAM_DQ9: U2.23, U3.30
/fpga/RAM_DQ10: U2.24, U3.31
/fpga/RAM_DQ11: U2.25, U3.32
/fpga/RAM_DQ12: U2.26, U3.35
/fpga/RAM_DQ13: U2.27, U3.36
/fpga/RAM_DQ14: U2.28, U3.37
/fpga/RAM_DQ15: U2.35, U3.38
/fpga/RAM_OE: U2.34, U3.41
/fpga/RAM_WE: U2.121, U3.17
/fpga/ROM_CS0: R19.2, U2.85, U5.7
/fpga/ROM_CS1: R23.2, U2.75, U6.7
/fpga/ROM_IO0: U2.83, U5.15, U6.15
/fpga/ROM_IO1: U2.74, U5.8, U6.8
/fpga/ROM_IO2: R26.2, U2.73, U5.9, U6.9
/fpga/ROM_IO3: R29.2, U2.76, U5.1, U6.1
/fpga/ROM_SCK: C34.1, R21.2, R22.1, U2.84, U5.16, U6.16
/fpga/RTC_SCL: R18.2, U2.125, U4.6
/fpga/RTC_SDA: R16.2, U2.126, U4.5
/fpga/TCK: CON4.4, U2.131
/fpga/TDI: CON4.2, U2.136
/fpga/TDO: CON4.3, U2.137
/fpga/TEST1: TP1.1, U2.112
/fpga/TEST2: TP2.1, U2.109
/fpga/TEST3: TP3.1, U2.111
/fpga/TEST4: TP4.1, U2.110
/fpga/TMS: CON4.1, U2.130
/fpga/UART_RX: CON3.3, R3.2, U1.1, U2.113
/fpga/UART_TX: CON3.4, R4.2, U1.5, U2.114
/fpga/USB_DETECT: JP5.1, R1.2, R2.1, U1.19, U2.115
/memory/RAM_CS: Q1.3, R32.2, U3.6
/memory/RAM_VDD: C22.1, C28.1, D9.3, R32.1, U3.11, U3.33
/memory/ROM_VIO: C36.1, C37.1, JP7.2, U5.14, U6.14
/memory/VBAT: BT1.1, D9.1, JP6.2
/memory/VBAT_JP: JP6.1, U4.3
/power/+3V3_REG: C20.1, D6.2, D8.2, U8.2, U8.4
/power/USB_VCC: C18.1, C19.1, D1.1, D6.1, U8.3
/usb_uart/FTDI_VCC: C30.1, D2.1, U1.20
/usb_uart/FT_3V3: C1.2, U1.4, U1.17
/usb_uart/USBD+: CON2.3, U1.15
/usb_uart/USBD-: CON2.2, U1.16
/usb_uart/USB_VBUS: C29.1, D1.2, D2.2, L1.1, R1.1
/usb_uart/VBUS: C31.1, CON2.1, L1.2
GND: BT1.2, C1.1, C2.2, C3.2, C4.2, C5.2, C6.2, C7.2, C8.2, C9.2, C10.2, C11.2, C12.2, C13.2, C14.2, C15.2, C16.2, C17.2, C18.2, C19.2, C20.2, C21.2, C22.2, C23.2, C24.2, C25.1, C26.2, C27.2, C28.2, C29.2, C30.2, C31.2, C32.2, C33.2, C34.2, C35.2, C36.2, C37.2, CON1.1, CON1.2, CON1.6, CON1.22, CON1.23, CON1.25, CON1.26, CON1.27, CON1.31, CON1.47, CON1.48, CON1.50, CON2.5, CON3.2, CON4.5, CON5.2, CON5.5, CON5.8, CON5.11, GND1.1, GND2.1, GND3.1, GND4.1, JP1.2, JP2.2, JP3.2, JP4.2, Q1.2, R2.2, R12.2, R13.2, R14.2, R15.2, R17.2, R22.2, R25.2, R27.2, U1.7, U1.18, U1.21, U1.25, U1.26, U2.8, U2.18, U2.29, U2.46, U2.53, U2.64, U2.80, U2.90, U2.101, U2.116, U2.124, U2.134, U3.12, U3.34, U3.39, U3.40, U4.4, U5.10, U6.10, U7.4, U8.1
unnamed: C23.1, U4.2, Y1.2
unnamed: C24.1, U4.1, Y1.1
unnamed: C35.1, CON2.6, R27.1
unnamed: LD1.1, R12.1
unnamed: LD2.1, R13.1
unnamed: LD3.1, R14.1
unnamed: LD4.1, R15.1

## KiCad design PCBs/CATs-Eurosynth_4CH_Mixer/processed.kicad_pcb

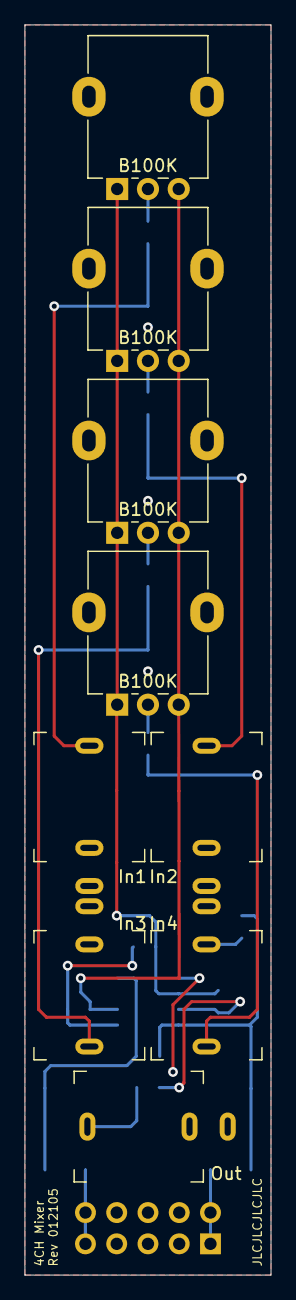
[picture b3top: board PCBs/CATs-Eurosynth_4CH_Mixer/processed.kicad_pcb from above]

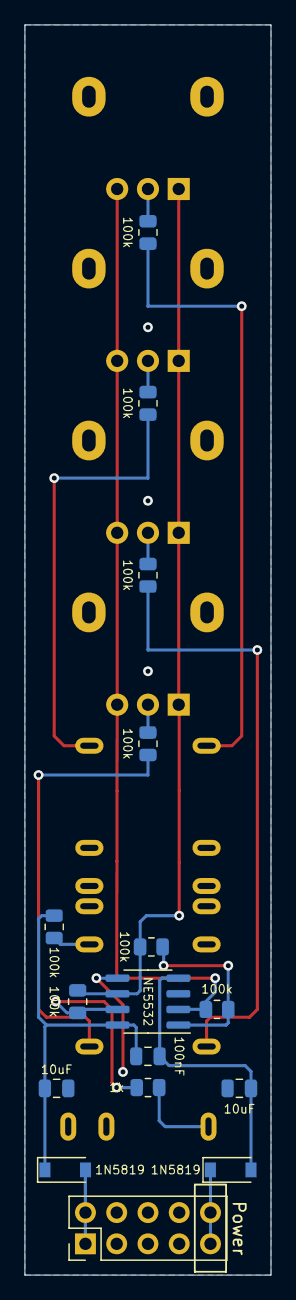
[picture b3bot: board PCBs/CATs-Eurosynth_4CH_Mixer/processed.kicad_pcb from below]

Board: 2 copper layers, 20.0 x 101.6 mm, 25 parts (16 on the bottom side), 19 nets.

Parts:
C1: 100nF; C_0805_2012Metric
C2, C3: 10uF; C_0805_2012Metric
D1, D2: 1N5819; D_SOD-123
IC1: NE5532; SOIC-8_3.9x4.9mm_P1.27mm
J1: In1; PJ-301-M-12
J2: In2; PJ-301-M-12
J3: In3; PJ-301-M-12
J4: In4; PJ-301-M-12
J5: Power; PinHeader_2x05_P2.54mm_Vertical
J6: Out; PJ-301-M-12
P1, P2, P3, P4: B100K; Potentiometer_Alpha_RD901F-40-00D_Single_Vertical
R4, R5, R6, R7, R8, R9, R10, R11: 100k; R_0805_2012Metric
R12: 1k; R_0805_2012Metric

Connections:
+12V: C1.1, C2.1, D1.1, IC1.8, R4.1
+12VA: D1.2, J5.1, J5.2
-12V: C1.2, C3.2, D2.2, IC1.4
-12VA: D2.1, J5.9, J5.10
GND: C2.2, C3.1, IC1.3, IC1.5, J1.S, J1.TN, J2.S, J2.TN, J3.S, J3.TN, J4.S, J5.3, J5.4, J5.5, J5.6, J5.7, J5.8, J6.S
unnamed: IC1.1, R9.1, R10.2
unnamed: IC1.7, R11.1, R12.2
unnamed: J1.T, R5.2
unnamed: J2.T, R6.2
unnamed: J3.T, R7.2
unnamed: J4.T, R8.2
unnamed: J4.TN, R4.2
unnamed: J6.T, R12.1
unnamed: P1.2, R5.1
unnamed: P2.2, R6.1
unnamed: P3.2, R7.1
unnamed: P4.2, R8.1
Sum+: IC1.2, P1.3, P2.3, P3.3, P4.3, R9.2
Sum-: IC1.6, P1.1, P2.1, P3.1, P4.1, R10.1, R11.2
